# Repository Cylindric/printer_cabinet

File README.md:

# PrinterCabinet

# Key Components

## Hardware

The electronic designs are all made using [KiCad](http://kicad-pcb.org).

The actual KiCad project files are [here](Hardware/PrinterCabinet/).

Rendered output (schematic and board PDFs, gerbers and bom) are [here](Hardware/Output/). (Not always up-to-date with the schematics and boards, so use with caution)

### License

All hardware designs are licensed under the [CERN Open Hardware Licence v1.2](https://www.ohwr.org/licenses/cern-ohl/license_versions/v1.2).

Myriam Ayass, legal adviser of the Knowledge and Technology Transfer Group at CERN and author of the CERN OHL:

> In the spirit of knowledge sharing and dissemination, the CERN Open Hardware Licence (CERN OHL) governs the use, copying, modification and distribution of hardware design documentation, and the manufacture and distribution of products.
> 
> The CERN–OHL is to hardware what the General Public Licence (GPL) is to software. It defines the conditions under which a licensee will be able to use or modify the licensed material. The concept of ‘open-source hardware’ or ‘open hardware’ is not yet as well known or widespread as the free software or open-source software concept. However, it shares the same principles: anyone should be able to see the source (the design documentation in case of hardware), study it, modify it and share it.
> 
> In addition, if modifications are made and distributed, it must be under the same licence conditions – this is the ‘persistent’ nature of the licence, which ensures that the whole community will continue benefiting from improvements, in the sense that everyone will in turn be able to make modifications to these improvements.

## Software

### License

All software (firmware) are Copyright 2018 Mark Hanford and licensed under the [Apache License, Version 2.0](http://www.apache.org/licenses/LICENSE-2.0) (the "License");

> You may not use this file except in compliance with the License. You may obtain a copy of the License at
>
> http://www.apache.org/licenses/LICENSE-2.0
>
> Unless required by applicable law or agreed to in writing, software distributed under the License is distributed on an "AS IS" BASIS, WITHOUT WARRANTIES OR CONDITIONS OF ANY KIND, either express or implied.
> See the License for the specific language governing permissions and limitations under the License.

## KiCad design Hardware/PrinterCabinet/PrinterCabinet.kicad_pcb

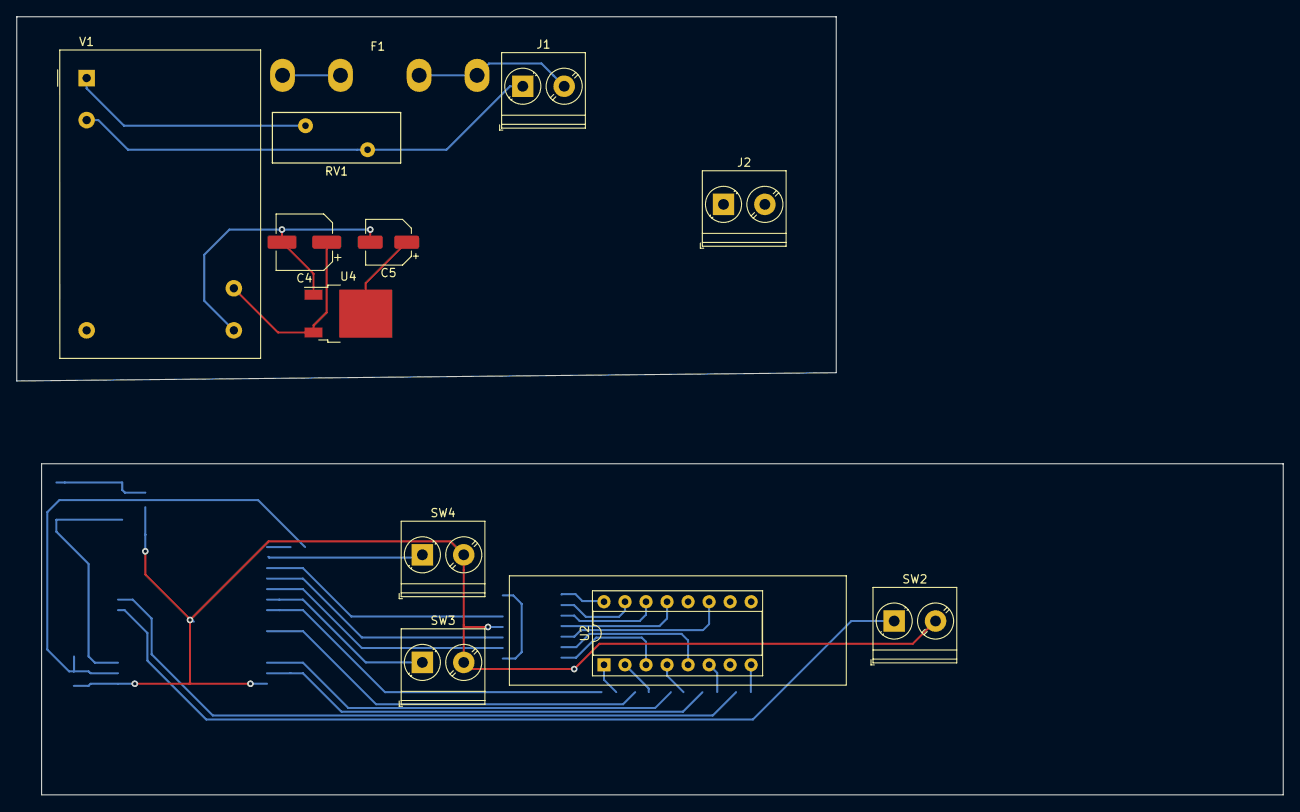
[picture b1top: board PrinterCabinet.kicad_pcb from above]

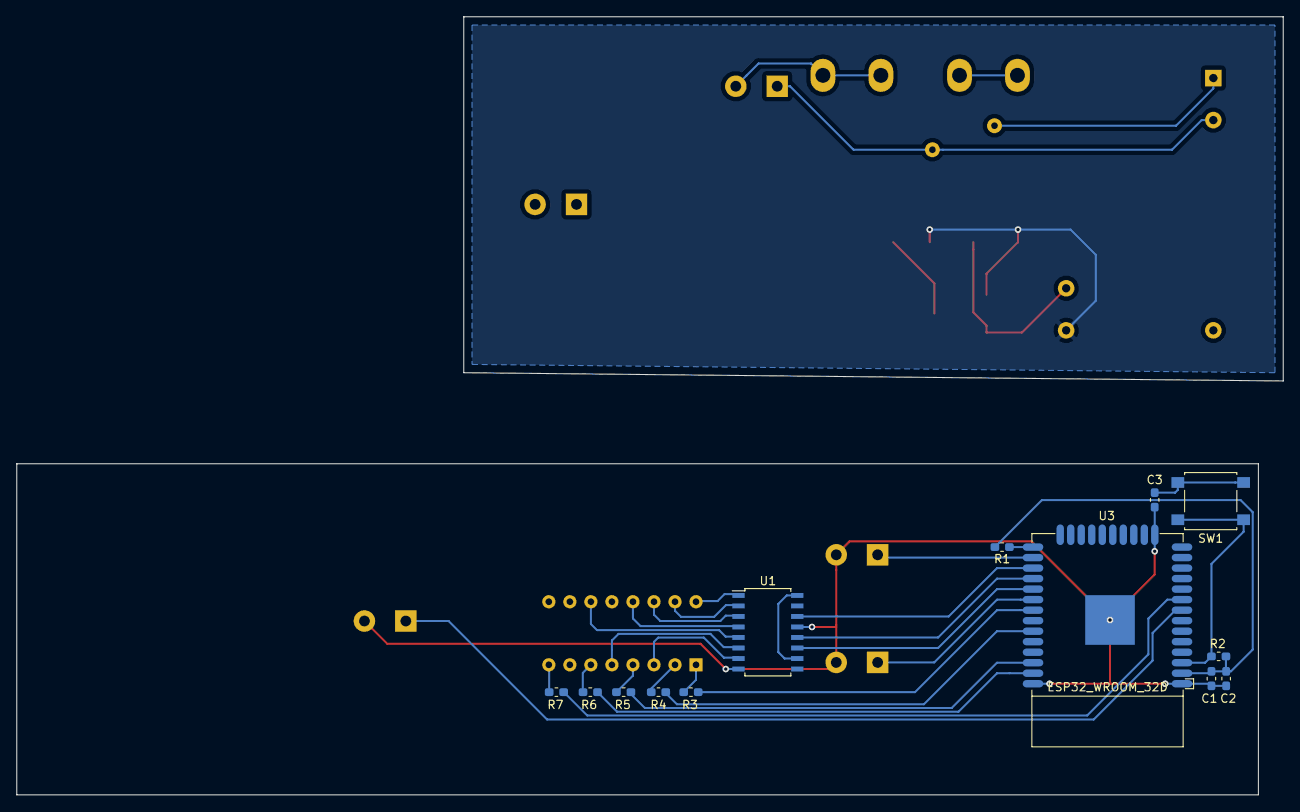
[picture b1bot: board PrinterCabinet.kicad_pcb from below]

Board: 2 copper layers, 153.0 x 94.0 mm, 25 parts (13 on the bottom side), 33 nets.

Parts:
C1: 10uF; C_0603_1608Metric_Pad1.05x0.95mm_HandSolder
C2, C3: 0.1uF; C_0603_1608Metric_Pad1.05x0.95mm_HandSolder
C4: 10uF; CP_Elec_6.3x5.4_Nichicon
C5: 4.7uF; CP_Elec_5x5.4
F1: 4A; Fuseholder_Glass_5mmx20mm
J1: MAINS_IN; TerminalBlock_Phoenix_PT-1,5-2-5.0-H_1x02_P5.00mm_Horizontal
J2: AIR_FILTER; TerminalBlock_Phoenix_PT-1,5-2-5.0-H_1x02_P5.00mm_Horizontal
R1, R2: 10k; R_0603_1608Metric_Pad1.05x0.95mm_HandSolder
R3, R4, R5, R6, R7: R; R_0603_1608Metric_Pad1.05x0.95mm_HandSolder
RV1: S14MOV; RV_Disc_D15.5mm_W6.1mm_P7.5mm
SW1: Reset; SW_SPST_B3S-1000
SW2: UV_STARTSTOP; TerminalBlock_Phoenix_PT-1,5-2-5.0-H_1x02_P5.00mm_Horizontal
SW3: UV_DOWN; TerminalBlock_Phoenix_PT-1,5-2-5.0-H_1x02_P5.00mm_Horizontal
SW4: UV_UP; TerminalBlock_Phoenix_PT-1,5-2-5.0-H_1x02_P5.00mm_Horizontal
U1: 74HC595; SOIC-16W_5.3x10.2mm_P1.27mm
U2: LTC-4627JR; DIP-16_W7.62mm_Socket
U3: ESP32-WROOM-32D; Espressif_ESP32_WROOM_32D_SMT
U4: NCP1117-3.3_TO252; TO-252-2
V1: 4W AC-DC Converter; Converter_ACDC_RECOM_RAC04-xxSGx_THT

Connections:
+3V3: C1.2, C2.1, C5.1, R1.2, R2.2, U3.2, U4.2
+12V: C4.1, U4.3, V1.5
/IO0: R1.1, U3.25
/LED_1: R3.1, U3.31
/LED_2: R4.1, U3.33
/LED_3: R6.1, U3.37
/LED_4: R7.1, U3.9
/LED_A: U1.3, U2.14
/LED_B: U1.1, U2.16
/LED_C: U1.4, U2.13
/LED_CLK: U1.11, U3.29
/LED_D: U1.7, U2.3
/LED_DATA: U1.14, U3.27
/LED_DOT: R5.1, U3.36
/LED_E: U1.6, U2.5
/LED_F: U1.5, U2.11
/LED_G: U1.2, U2.15
/LED_LATCH: U1.12, U3.28
/LIVE: RV1.1, V1.1
/NEUTRAL: J1.1, RV1.2, V1.2
/UNFUSED_LIVE: F1.2, J1.2
/UV_DOWN: SW3.1, U3.30
/UV_GO: SW2.1, U3.8
/UV_UP: SW4.1, U3.26
GND: C1.1, C2.2, C3.2, C4.2, C5.2, SW2.2, SW3.2, SW4.2, U1.8, U1.13, U3.1, U3.15, U3.38, U3.39, U4.1, V1.4
unnamed: C3.1, SW1.2
unnamed: R2.1, SW1.1, U3.3
unnamed: R3.2, U2.1
unnamed: R4.2, U2.2
unnamed: R5.2, U2.4
unnamed: R6.2, U2.6
unnamed: R7.2, U2.8
VCC: U1.10, U1.16

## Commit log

2019-11-22 Initial cabinet control hardware
